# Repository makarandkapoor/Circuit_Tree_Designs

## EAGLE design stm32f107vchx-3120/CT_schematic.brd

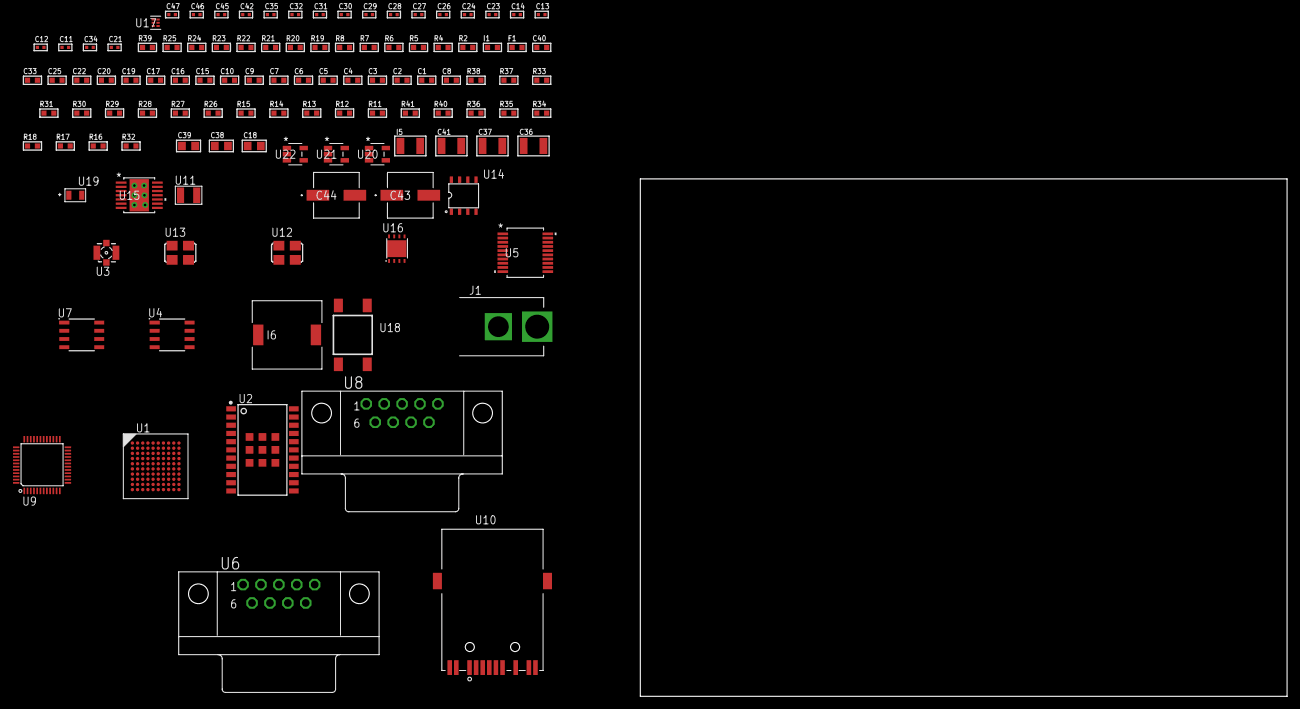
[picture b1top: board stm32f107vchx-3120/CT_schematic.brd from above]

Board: 2 copper layers, 100.0 x 80.0 mm, 111 parts (0 on the bottom side), 78 nets, no tracks yet.

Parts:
C1, C10, C15, C16, C17, C19, C20, C22, C25, C33, C40: 1e-06; C0603
C2, C3, C4, C5, C6, C7: 1e-07; C0603
C8: 4.7e-06; C0603
C9: 1e-08; C0603
C11, C12: 1e-11; C0402
C13, C23, C26, C28, C29, C35, C42: 1e-07; C0402
C14, C24, C27, C30, C31, C32, C45, C46, C47: 1e-08; C0402
C18: 4.7e-06; C0805
C21: 2.2e-08; C0402
C34: 3.3e-09; C0402
C36, C37: 2.2e-05; C1210
C38, C39: 1e-05; C0805
C41: 1e-05; C1210
C43, C44: 0.0001; EXV-9H
F1: 240.0; L0603
I1: 97.0; R0603
I5: 1.5e-05; L1210
I6: 5.2e-06; DR1040
J1: PJ-037B; PJ-037B_PACKAGE
R2: 1000.0; R0603
R4, R5, R6, R25: 4700.0; R0603
R7, R8: 2200.0; R0603
R11, R12, R13, R14, R15, R26, R27, R28, R29, R30, R31, R37, R38: 10000.0; R0603
R16, R17, R18, R34, R36: 100000.0; R0603
R19: 120.0; R0603
R20, R21: 0.1; R0603
R22, R23: 200.0; R0603
R24: 2490.0; R0603
R32: 71007.101651032; R0603
R33: 22000.0; R0603
R35: 300000.0; R0603
R39: 9100.0; R0603
R40: 680000.0; R0603
R41: 120000.0; R0603
U1: stm32f107vch6; LFBGA100
U2: A2200-A
U3: 73412-0114; COAXIAL_C
U4: AT25040B-SSHL-T; SOIC-8
U5: MAX3218EAP+T; SSOP-20
U6, U8: 182-009-113R531; 182-009-MALE
U7: MCP2562-E/SN; SOIC-8
U9: RTL8201FL-VB-CG
U10: 7498011122R
U11: ABS07-32.768KHZ-7-T
U12: ASFL1-25MHZ-NCS; ASFL1
U13: ASFL1-50MHZ-NCS; ASFL1
U14: idt74fct38072; IDT74FCT38072
U15: tps54225PWP; HTSSOP14
U16: LP2951ACSDX/NOPB; WSON-8
U17: TPS3895ADRYR; SON-6
U18: 4-1437565-2; SW_4-1437565-2
U19: Q65110A2395; LGM67K-G1J2-24-Z
U20, U21, U22: nc7sz125m5x; NC7SZ125M5X

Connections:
CLK_CRYSTAL_U1_A1: C11.1, U1.A1, U11.1
CLK_CRYSTAL_U1_B1: C12.1, U1.B1, U11.2
CLK_U1_C1: U1.C1, U12.3
CLK_U1_H2: U1.H2, U14.7
CLK_U9_43: U9.43, U14.6
CLK_U14_3: U13.3, U14.3
GND: C1.2, C2.2, C3.2, C4.2, C5.2, C6.2, C7.2, C8.2, C9.2, C10.2, C11.2, C12.2, C13.2, C14.2, C15.2, C16.2, C17.2, C19.2, C20.2, C21.2, C22.2, C23.2, C24.2, C25.2, C26.2, C27.2, C28.2, C29.2, C30.2, C31.2, C32.2, C33.2, C34.2, C36.2, C37.2, C38.2, C39.2, C40.2, C41.2, C42.2, C43.2, C44.2, C45.2, C46.2, C47.2, J1.2, R2.2, R11.2, R20.2, R21.2, R24.2, R29.2, R33.2, R36.2, R39.2, R41.2, U1.C2, U1.E4, U1.E5, U1.E6, U1.E7, U1.G1, U1.H1, U2.7, U2.8, U2.23, U2.24, U2.25, U2.26, U2.27, U2.28, U2.29, U2.30, U2.31, U4.4, U5.5, U5.17, U5.20, U6.5, U7.2, U7.8, U8.5, U9.7, U9.20, U9.33, U9.42, U9.47, U12.2, U13.2, U14.4, U14.5, U14.8, U15.5, U15.8, U15.9, U15.15, U16.3, U16.4, U16.PAD, U17.2, U19.C, U20.1, U20.3, U21.1, U21.3, U22.1, U22.3
NET_U1_A5: R8.1, U1.A5, U2.16
NET_U1_B4: R7.1, U1.B4, U2.15
NET_U1_D5: R11.1, U1.D5
NET_U1_E1: R6.1, U1.E1, U22.4
NET_U1_K1: C9.1, C10.1, F1.1, U1.J1, U1.K1
NET_U1_K10: U18.3, U18.4
NET_U2_2: R12.2, U2.2
NET_U2_17: R12.1, U2.17
NET_U2_22: R5.1, U2.22, U21.4
NET_U3_1: U2.11, U3.1
NET_U3_2: U2.10, U3.2, U3.3, U3.4
NET_U4_3: R13.1, U4.3
NET_U4_7: R15.1, U4.7
NET_U5_1: I5.1, U5.1
NET_U5_2: R16.1, U5.2
NET_U5_3: R17.1, U5.3
NET_U5_4: R18.1, U5.4
NET_U5_15: C17.1, U5.15
NET_U5_16: C18.2, U5.16
NET_U5_18: C18.1, U5.18
NET_U5_19: C16.1, U5.19
NET_U6_2: U5.12, U6.2
NET_U6_3: U5.14, U6.3
NET_U6_7: U5.11, U6.7
NET_U6_8: U5.13, U6.8
NET_U7_6: R19.2, U7.6
NET_U8_2: R19.2, U7.6, U8.2
NET_U8_3: R19.1, U7.7, U8.3
NET_U9_6: C22.1, C23.1, C24.1, I1.1, U9.6, U9.41
NET_U9_10: R29.1, U9.10
NET_U9_13: R26.1, U9.13
NET_U9_18: R30.1, U9.18
NET_U9_29: R4.1, U9.29, U20.4
NET_U9_32: R25.1, U9.32
NET_U9_34: R27.1, U9.34
NET_U9_35: R28.1, U9.35
NET_U9_39: R31.1, U9.39
NET_U9_40: C29.1, U9.40
NET_U9_46: R24.1, U9.46
NET_U9_48: C28.1, U9.48
NET_U10_1: U9.1, U10.1
NET_U10_3: U9.2, U10.3
NET_U10_4: U9.4, U10.4
NET_U10_5: C21.1, U10.2, U10.5
NET_U10_6: U9.5, U10.6
NET_U10_8: R21.1, U10.8
NET_U10_10: R22.1, U10.10
NET_U10_12: R23.1, U10.12
NET_U10_13: R20.1, U10.13, U10.14
NET_U15_2: R32.2, R33.1, U15.2
NET_U15_3: C33.1, U15.3
NET_U15_4: C34.1, U15.4
NET_U15_10: C35.1, I6.1, U15.10, U15.11
NET_U15_12: C35.2, U15.12
NET_U16_5: R34.1, U16.5
NET_U16_7: R35.2, R36.1, U16.7
NET_U17_1: R38.1, R39.1, U17.1
NET_U17_3: R40.2, R41.1, U17.3
NET_U17_4: R37.1, U17.4, U20.2, U21.2, U22.2
NET_U18_1: R2.1, U18.1, U18.2
PROC_CAN1_RX: U1.C10, U7.4
PROC_CAN1_TX: U1.A4, U7.1
PROC_SPI1_MISO: U1.A6, U4.2
PROC_SPI1_MOSI: U1.C5, U4.5
PROC_SPI1_NSS: R14.1, U1.A8, U4.1
PROC_SPI1_SCK: U1.A7, U4.6
PROC_UART4_RX: U1.B8, U5.9
PROC_UART4_TX: U1.B9, U5.7
VCC_S1_6V4: C38.1, C39.1, C40.1, C43.1, C44.1, J1.1, U15.7, U15.13, U15.14, U16.8
VCC_TIER1_3V3: C1.1, C2.1, C3.1, C4.1, C5.1, C6.1, C7.1, C8.1, C13.1, C14.1, C15.1, C20.1, C25.1, C26.1, C27.1, C30.1, C31.1, C32.1, C36.1, C37.1, C42.1, C45.1, C46.1, C47.1, F1.2, I1.2, I5.2, I6.2, R4.2, R5.2, R6.2, R7.2, R8.2, R13.2, R14.2, R15.2, R16.2, R17.2, R18.2, R25.2, R26.2, R27.2, R28.2, R30.2, R31.2, R32.1, R37.2, R38.2, R40.1, U1.B2, U1.D2, U1.F4, U1.F5, U1.F6, U1.F7, U2.20, U4.8, U5.6, U7.5, U9.15, U9.21, U9.37, U10.9, U10.11, U12.4, U13.4, U14.1, U14.2, U15.1, U17.6, U20.5, U21.5, U22.5
VCC_TIER1_5V0: C19.1, C41.1, R34.2, R35.1, U7.3, U16.1

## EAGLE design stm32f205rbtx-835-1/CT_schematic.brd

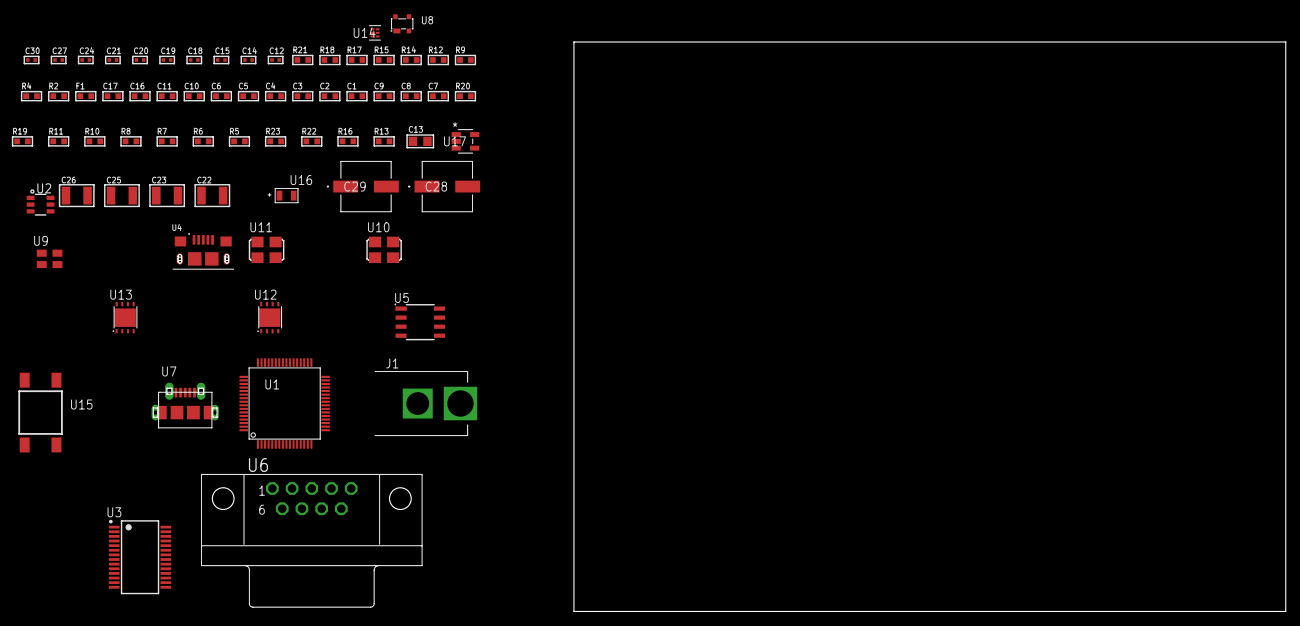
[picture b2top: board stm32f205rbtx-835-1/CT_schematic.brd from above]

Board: 2 copper layers, 70 parts (0 on the bottom side), 43 nets, no tracks yet.

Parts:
C1, C11, C16, C17: 1e-06; C0603
C2, C3, C4, C5, C6: 1e-07; C0603
C7: 4.7e-06; C0603
C8, C9: 2.2e-06; C0603
C10: 1e-08; C0603
C12, C14, C15, C27: 1e-07; C0402
C13: 4.7e-06; C0805
C18, C19, C20, C21, C24, C30: 1e-08; C0402
C22, C23, C25, C26: 1e-05; C1210
C28, C29: 0.0001; EXV-9H
F1: 240.0; L0603
J1: PJ-037B; PJ-037B_PACKAGE
R2, R15, R18: 1000.0; R0603
R4, R9: 4700.0; R0603
R5: 47000.0; R0603
R6, R7, R8, R10, R11, R19, R20: 10000.0; R0603
R12: 120.0; R0603
R13, R16: 100000.0; R0603
R14: 2231.0; R0603
R17: 3900.0; R0603
R21: 9100.0; R0603
R22: 680000.0; R0603
R23: 120000.0; R0603
U1: STM32F205RBT7; LQFP64
U2: MAX4995AAUT+T; SOT-23-6
U3: FT232RL-REEL; SSOP-28
U4: 10118193-0001LF; FCI_10118193-0001LF
U5: MCP2562-E/SN; SOIC-8
U6: 182-009-113R531; 182-009-MALE
U7: 47590-0001; MICRO_USB_AB
U8: prtr5v0u2ax; SOT143B
U9: ASEK-32.768KHz-ECST; ASEK
U10: ASFL1-12MHZ-NCS; ASFL1
U11: ASFL1-25MHZ-NCS; ASFL1
U12, U13: LP3878SDX-ADJ/NOPB; WSON-8
U14: TPS3895ADRYR; SON-6
U15: 4-1437565-2; SW_4-1437565-2
U16: Q65110A2395; LGM67K-G1J2-24-Z
U17: nc7sz125m5x; NC7SZ125M5X

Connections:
CLK_U1_3: U1.3, U9.3
CLK_U1_5: U1.5, U11.3
CLK_U3_27: U3.27, U10.3
GND: C1.2, C2.2, C3.2, C4.2, C5.2, C6.2, C7.2, C8.2, C9.2, C10.2, C11.2, C12.2, C13.2, C14.2, C15.2, C16.2, C17.2, C18.2, C19.2, C20.2, C21.2, C22.2, C23.2, C24.2, C25.2, C26.2, C27.2, C28.2, C29.2, C30.2, J1.2, R2.2, R5.2, R6.2, R8.2, R11.2, R15.2, R18.2, R21.2, R23.2, U1.12, U1.18, U1.63, U2.2, U3.7, U3.18, U3.21, U3.25, U3.26, U4.5, U4.6, U4.7, U4.8, U4.9, U5.2, U5.8, U6.5, U7.5, U7.6, U7.7, U7.8, U7.9, U8.1, U9.2, U10.2, U11.2, U12.3, U12.PAD, U13.3, U13.PAD, U14.2, U16.C, U17.1, U17.3
NET_U1_7: R4.1, U1.7, U17.4
NET_U1_13: C10.1, C11.1, F1.1, U1.13
NET_U1_31: C8.1, U1.31
NET_U1_47: C9.1, U1.47
NET_U1_59: U15.3, U15.4
NET_U1_60: R6.1, U1.60
NET_U2_3: R5.1, U2.3
NET_U3_14: R10.1, U3.14
NET_U3_17: C14.1, U3.17
NET_U3_19: R11.1, U3.19
NET_U4_1: R9.1, U4.1
NET_U4_2: U3.16, U4.2
NET_U4_3: U3.15, U4.3
NET_U5_6: R12.2, U5.6
NET_U6_2: R12.2, U5.6, U6.2
NET_U6_3: R12.1, U5.7, U6.3
NET_U12_1: C21.1, U12.1
NET_U12_6: R14.2, R15.1, U12.6
NET_U12_8: R13.1, U12.8
NET_U13_1: C24.1, U13.1
NET_U13_6: R17.2, R18.1, U13.6
NET_U13_8: R16.1, U13.8
NET_U14_1: R20.1, R21.1, U14.1
NET_U14_3: R22.2, R23.1, U14.3
NET_U14_4: R19.1, U14.4, U17.2
NET_U15_1: R2.1, U15.1, U15.2
PROC_CAN1_RX: U1.61, U5.4
PROC_CAN1_TX: U1.62, U5.1
PROC_GPIO_TO_U1_USB_FAULT: R7.1, U1.4, U2.6
PROC_GPIO_TO_U1_VBUS_EN: R8.1, U1.2, U2.4
PROC_UART4_RX: U1.15, U3.1
PROC_UART4_TX: U1.14, U3.5
PROC_USB_OTG_FS_DM: U1.44, U7.2, U8.3
PROC_USB_OTG_FS_DP: U1.45, U7.3, U8.2
PROC_USB_OTG_FS_ID: U1.43, U7.4
PROC_USB_OTG_FS_VBUS: U1.42, U2.1, U7.1, U8.4
VCC_S1_13V4: C22.1, C25.1, C28.1, C29.1, J1.1, R13.2, R16.2, U12.4, U13.4
VCC_TIER1_3V3: C1.1, C2.1, C3.1, C4.1, C5.1, C6.1, C7.1, C12.1, C13.1, C15.1, C17.1, C18.1, C19.1, C20.1, C23.1, C27.1, C30.1, F1.2, R4.2, R7.2, R10.2, R14.1, R19.2, R20.2, R22.1, U1.1, U1.19, U1.32, U1.48, U1.64, U3.4, U3.20, U5.5, U9.4, U10.4, U11.4, U12.5, U14.6, U17.5
VCC_TIER1_5V0: C16.1, C26.1, R17.1, U2.5, U5.3, U13.5

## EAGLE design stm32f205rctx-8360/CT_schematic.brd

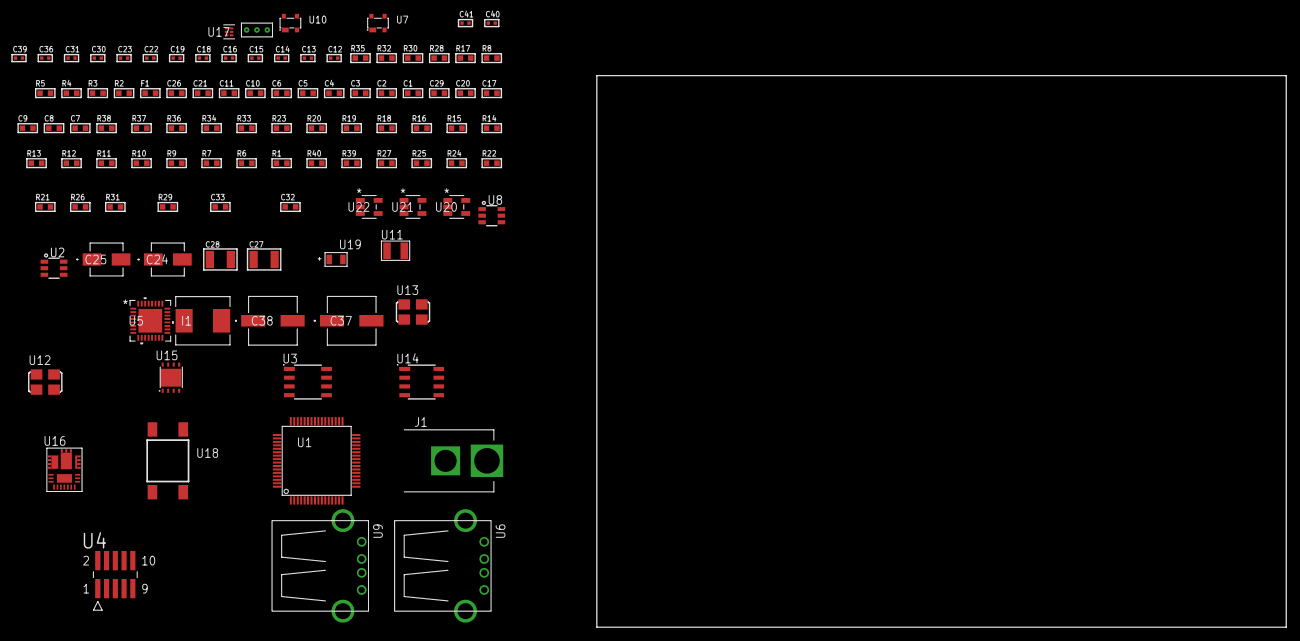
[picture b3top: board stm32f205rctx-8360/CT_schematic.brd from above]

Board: 2 copper layers, 100.0 x 80.0 mm, 105 parts (0 on the bottom side), 76 nets, no tracks yet.

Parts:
C1, C11: 1e-06; C0603
C2, C3, C4, C5, C6: 1e-07; C0603
C7: 4.7e-06; C0603
C8, C9, C17, C20, C29: 2.2e-06; C0603
C10: 1e-08; C0603
C12, C13: 1e-11; C0402
C14, C22, C23, C39, C40, C41: 1e-08; C0402
C15, C16, C18, C19, C30, C31, C36: 1e-07; C0402
C21: 0.0001; R0603
C24: 1e-06; EXV-9B
C25: 2.2e-06; EXV-9B
C26: 8e-07; R0603
C27: 1e-05; C1210
C28: 0.0001; C1210
C32: 8.8006443804346e-09; R0603
C33: 3.0002196751482e-07; R0603
C37, C38: 0.0001; EXV-9H
F1: 240.0; L0603
I1: 6.8e-07; IND25X25CZ
J1: PJ-037B; PJ-037B_PACKAGE
R1, R7, R9, R10, R11, R12, R13, R14, R15, R16, R19, R20, R36, R37: 10000.0; R0603
R2: 1000.0; R0603
R3: 910.0; R0603
R4, R5: 4700.0; R0603
R6, R18, R23: 47000.0; R0603
R8: 1270.0; R0603
R17: 5.0; R0603
R21, R22, R24, R25, R27: 100000.0; R0603
R26: 153694.38; R0603
R28: 0.1; R0603
R29: 4030.2416170974; R0603
R30: 453.0; R0603
R31: 57.923764705882; R0603
R32: 130.0; R0603
R33: 39000.0; R0603
R34: 49900.0; R0603
R35: 5100.0; R0603
R38: 82000.0; R0603
R39: 300000.0; R0603
R40: 120000.0; R0603
U1: STM32F205RCT7; LQFP64
U2, U8: MAX4995AAUT+T; SOT-23-6
U3: AT25010B-SSHL-T; SOIC-8
U4: FTSH-105-01-L-DV-K; SAMTEC_FTSH-105-01-L-DV-K
U5: TUSB1210BRHBR; RHB32_3P45X3P45
U6, U9: 61400416021; USB-A-H
U7, U10: prtr5v0u2ax; SOT143B
U11: ABS07-32.768KHZ-7-T
U12: ASFL1-19.2MHZ-NCS; ASFL1
U13: ASFL1-25MHZ-NCS; ASFL1
U14: LP2954AIMX/NOPB; LP2954
U15: LP2951ACSDX/NOPB; WSON-8
U16: IR3899MTR1PBF
U17: TPS3895ADRYR; SON-6
U18: 4-1437565-2; SW_4-1437565-2
U19: Q65110A2395; LGM67K-G1J2-24-Z
U20, U21, U22: nc7sz125m5x; NC7SZ125M5X
U23: Dummy; DUMMY_PACKAGE_226

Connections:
CLK_CRYSTAL_U1_3: C12.1, U1.3, U11.1
CLK_CRYSTAL_U1_4: C13.1, U1.4, U11.2
CLK_U1_5: U1.5, U13.3
CLK_U5_1: U5.1, U12.3
GND: C1.2, C2.2, C3.2, C4.2, C5.2, C6.2, C7.2, C8.2, C9.2, C10.2, C11.2, C12.2, C13.2, C14.2, C15.2, C16.2, C17.2, C18.2, C19.2, C20.2, C21.2, C22.2, C23.2, C24.2, C25.2, C26.2, C27.2, C29.2, C30.2, C31.2, C36.2, C37.2, C38.2, C39.2, C40.2, C41.2, J1.2, R2.2, R6.2, R7.2, R8.2, R10.2, R17.2, R18.2, R20.2, R24.2, R27.2, R28.1, R28.2, R30.2, R33.2, R35.2, R38.2, R40.2, U1.12, U1.18, U1.63, U2.2, U3.4, U4.3, U4.5, U5.23, U5.33, U6.4, U6.5, U6.6, U7.1, U8.2, U9.4, U9.5, U9.6, U10.1, U12.2, U13.2, U14.4, U15.3, U15.4, U15.PAD, U16.4, U16.11, U16.17, U17.2, U19.C, U20.2, U20.3, U21.1, U21.3, U22.1, U22.3, U23.1
NET_U1_7: R4.1, U1.7, U21.4
NET_U1_13: C10.1, C11.1, F1.1, U1.13
NET_U1_31: C8.1, U1.31
NET_U1_47: C9.1, U1.47
NET_U1_60: R7.1, U1.60
NET_U1_61: R3.1, U1.61, U19.A
NET_U1_62: R1.1, U1.62, U18.3, U18.4
NET_U2_3: R6.1, U2.3
NET_U3_3: R11.1, U3.3
NET_U3_7: R13.1, U3.7
NET_U4_9: R17.1, U4.9
NET_U5_11: R19.1, U5.11
NET_U5_12: C20.1, U5.12
NET_U5_14: R20.1, U5.14
NET_U5_20: C17.1, U5.20
NET_U5_27: R5.1, U5.27, U22.4
NET_U6_1: C21.1, U5.22, U6.1, U7.4, U8.1
NET_U6_2: U5.19, U6.2, U7.3
NET_U6_3: U5.18, U6.3, U7.2
NET_U8_3: R18.1, U8.3
NET_U8_4: U5.17, U8.4
NET_U14_3: R22.1, U14.3
NET_U14_5: R21.1, U14.5
NET_U14_7: R23.2, R24.1, U14.7
NET_U15_5: R25.1, U15.5
NET_U15_7: R26.2, R27.1, U15.7
NET_U16_1: C32.1, R29.1, R30.1, R31.1, R32.1, U16.1, U16.8
NET_U16_2: C31.1, U16.2
NET_U16_3: C32.2, C33.1, C33.2, U16.3
NET_U16_5: R33.1, U16.5
NET_U16_10: C29.1, U16.10
NET_U16_12: C28.1, I1.1, U16.12
NET_U16_14: C28.2, U16.14
NET_U16_15: R34.1, R35.1, U16.15
NET_U16_ATNET_3: I1.2, R29.2
NET_U16_ATNET_4: C33.2, R31.2
NET_U17_1: R37.1, R38.1, U17.1
NET_U17_3: R39.2, R40.1, U17.3
NET_U17_4: R36.1, U17.4, U20.4, U21.2, U22.2
NET_U18_1: R2.1, U18.1, U18.2
PROC_GPIO_TO_U1_USB_FAULT: R9.1, U1.6, U2.6
PROC_GPIO_TO_U1_VBUS_EN: R10.1, U1.2, U2.4
PROC_SPI3_MISO: U1.52, U3.2
PROC_SPI3_MOSI: U1.53, U3.5
PROC_SPI3_NSS: R12.1, U1.20, U3.1
PROC_SPI3_SCK: U1.51, U3.6
PROC_SYS_JTCK_SWCLK: R15.1, U1.49, U4.4
PROC_SYS_JTDO_SWO: U1.55, U4.6
PROC_SYS_JTMS_SWDIO: R16.1, U1.46, U4.2
PROC_TIM1_CH1: U1.41, U23.3
PROC_TIM1_CH3: R8.1, U1.43, U23.2
PROC_USB_OTG_FS_DM: U1.44, U9.2, U10.3
PROC_USB_OTG_FS_DP: U1.45, U9.3, U10.2
PROC_USB_OTG_FS_VBUS: U1.42, U2.1, U9.1, U10.4
PROC_USB_OTG_HS_ULPI_CK: U1.21, U5.26
PROC_USB_OTG_HS_ULPI_D0: U1.17, U5.3
PROC_USB_OTG_HS_ULPI_D1: U1.26, U5.4
PROC_USB_OTG_HS_ULPI_D2: U1.27, U5.5
PROC_USB_OTG_HS_ULPI_D3: U1.29, U5.6
PROC_USB_OTG_HS_ULPI_D4: U1.30, U5.7
PROC_USB_OTG_HS_ULPI_D5: U1.33, U5.9
PROC_USB_OTG_HS_ULPI_D6: U1.34, U5.10
PROC_USB_OTG_HS_ULPI_D7: U1.57, U5.13
PROC_USB_OTG_HS_ULPI_DIR: U1.10, U5.31
PROC_USB_OTG_HS_ULPI_NXT: U1.11, U5.2
PROC_USB_OTG_HS_ULPI_STP: U1.8, U5.29
RST_OUT_U4_JTAG_RST_B: R14.1, U4.10, U20.1
VCC_S1_17V0: C24.1, C26.1, C30.1, C37.1, C38.1, J1.1, R22.2, R34.2, U14.8, U15.8, U16.9
VCC_TIER1_1V8: C1.1, C2.1, C3.1, C4.1, C5.1, C6.1, C7.1, C14.1, C15.1, C18.1, C19.1, C25.1, C36.1, C39.1, C40.1, C41.1, F1.2, R1.2, R3.2, R4.2, R5.2, R9.2, R11.2, R12.2, R13.2, R14.2, R15.2, R16.2, R19.2, R21.2, R23.1, R36.2, R37.2, R39.1, U1.1, U1.19, U1.32, U1.48, U1.64, U3.8, U4.1, U5.28, U5.30, U5.32, U14.1, U17.6, U20.5, U21.5, U22.5
VCC_TIER1_3V3: C16.1, C22.1, C23.1, C27.1, R25.2, R26.1, U5.21, U12.4, U13.4, U15.1
VCC_TIER1_5V0: I1.2, R29.2, U2.5, U8.5

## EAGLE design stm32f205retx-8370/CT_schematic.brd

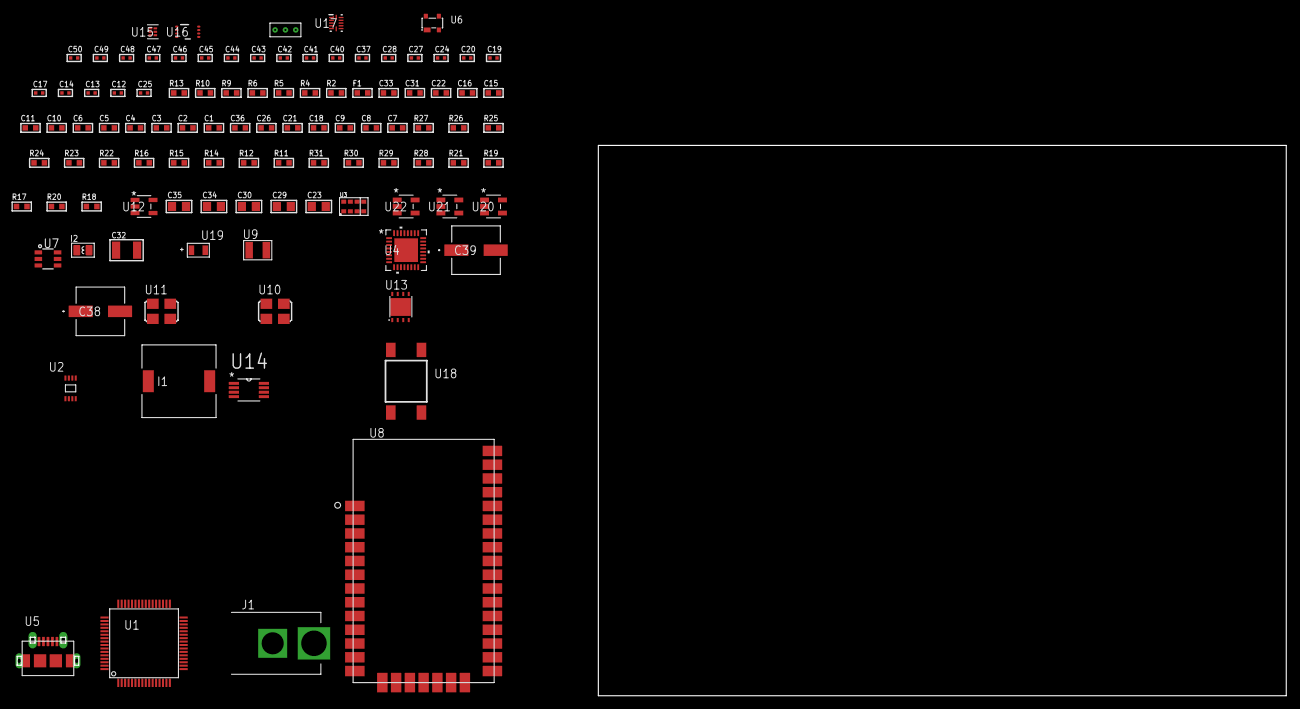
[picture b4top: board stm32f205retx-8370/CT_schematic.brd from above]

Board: 2 copper layers, 104 parts (0 on the bottom side), 65 nets, no tracks yet.

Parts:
C1, C11, C15, C16, C22, C31, C33: 1e-06; C0603
C2, C3, C4, C5, C6: 1e-07; C0603
C7: 4.7e-06; C0603
C8, C9, C18, C21: 2.2e-06; C0603
C10: 1e-08; C0603
C12, C13: 1e-11; C0402
C14, C27, C28, C40, C42, C44, C46, C48, C49, C50: 1e-08; C0402
C17, C19, C20, C24, C37, C41, C43, C45, C47: 1e-07; C0402
C23, C29, C30, C34, C35: 1e-05; C0805
C25: 4.7e-11; C0402
C26: 8.2e-12; C0603
C32: 1e-05; C1210
C36: 1.6e-09; C0603
C38, C39: 0.0001; EXV-9H
F1: 240.0; L0603
I1: 7e-06; DR1040
I2: 3.3e-06; L0806
J1: PJ-037B; PJ-037B_PACKAGE
R2: 1000.0; R0603
R4, R5, R6: 4700.0; R0603
R9, R10: 2200.0; R0603
R11, R12, R15, R16, R25, R26: 10000.0; R0603
R13: 22.0; R0603
R14, R22: 47000.0; R0603
R17: 490000.0; R0603
R18: 1000000.0; R0603
R19, R21: 100000.0; R0603
R20: 153694.38; R0603
R23: 56000.0; R0603
R24: 18000.0; R0603
R27: 82000.0; R0603
R28: 300000.0; R0603
R29: 120000.0; R0603
R30, R31: 200000.0; R0603
U1: STM32F205RET7; LQFP64
U2: 24AA02T-I/MNY; TDFN-8/6MM
U3: TMD27711; SMD-8
U4: TUSB1210BRHBR; RHB32_3P45X3P45
U5: 47590-0001; MICRO_USB_AB
U6: prtr5v0u2ax; SOT143B
U7: MAX4995AAUT+T; SOT-23-6
U8: XB24CZ7UIS-004
U9: ABS07-32.768KHZ-7-T
U10: ASFL1-19.2MHZ-NCS; ASFL1
U11: ASFL1-25MHZ-NCS; ASFL1
U12: ltc3406es5; TSOT-23-5
U13: LP2951ACSDX/NOPB; WSON-8
U14: TPS61085DGKR; MSOP-8
U15: TPS3895ADRYR; SON-6
U16: LSF0102DCTR; DCU0008A_N
U17: LSF0204DRUTR; RUT0012A
U18: 4-1437565-2; SW_4-1437565-2
U19: Q65110A2395; LGM67K-G1J2-24-Z
U20, U21, U22: nc7sz125m5x; NC7SZ125M5X
U23: Dummy; DUMMY_PACKAGE_217

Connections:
CLK_CRYSTAL_U1_3: C12.1, U1.3, U9.1
CLK_CRYSTAL_U1_4: C13.1, U1.4, U9.2
CLK_U1_5: U1.5, U11.3
CLK_U4_1: U4.1, U10.3
GND: C1.2, C2.2, C3.2, C4.2, C5.2, C6.2, C7.2, C8.2, C9.2, C10.2, C11.2, C12.2, C13.2, C14.2, C15.2, C16.2, C17.2, C18.2, C19.2, C20.2, C21.2, C22.2, C23.2, C24.2, C25.2, C26.2, C27.2, C28.2, C29.2, C30.1, C30.2, C31.2, C32.2, C33.2, C34.2, C35.1, C35.2, C36.1, C36.2, C37.2, C38.2, C39.2, C40.2, C41.2, C42.2, C43.2, C44.2, C45.2, C46.2, C47.2, C48.2, C49.2, C50.2, J1.2, R2.2, R11.2, R14.2, R16.2, R17.2, R21.2, R24.2, R27.2, R29.2, U1.12, U1.18, U1.63, U2.4, U3.3, U4.33, U5.5, U5.6, U5.7, U5.8, U5.9, U6.1, U7.2, U8.1, U8.11, U8.13, U8.22, U8.35, U10.2, U11.2, U12.2, U13.3, U13.4, U13.PAD, U14.4, U15.2, U16.1, U17.6, U19.C, U20.1, U20.3, U21.1, U21.3, U22.1, U22.3, U23.1
NET_U1_7: R5.1, U1.7, U21.4
NET_U1_13: C10.1, C11.1, F1.1, U1.13
NET_U1_31: C8.1, U1.31
NET_U1_40: R10.1, U1.40, U2.5
NET_U1_41: R9.1, U1.41, U2.6
NET_U1_47: C9.1, U1.47
NET_U1_60: R11.1, U1.60
NET_U1_62: U18.3, U18.4
NET_U3_4: C16.1, R13.1, U3.4
NET_U3_7: R12.1, U3.7
NET_U4_11: R15.1, U4.11
NET_U4_12: C21.1, U4.12
NET_U4_14: R16.1, U4.14
NET_U4_20: C18.1, U4.20
NET_U4_27: R6.1, U4.27, U22.4
NET_U5_1: C22.1, U4.22, U5.1, U6.4, U7.1
NET_U5_2: U4.19, U5.2, U6.3
NET_U5_3: U4.18, U5.3, U6.2
NET_U5_4: U4.23, U5.4
NET_U7_3: R14.1, U7.3
NET_U7_4: U4.17, U7.4
NET_U8_6: R4.1, U8.6, U20.4
NET_U12_3: I1.1, U12.3
NET_U12_5: R17.1, R18.1, U12.5
NET_U12_ATNET_3: I1.2, R18.2
NET_U13_5: R19.1, U13.5
NET_U13_7: R20.2, R21.1, U13.7
NET_U14_1: R22.1, U14.1
NET_U14_2: R23.1, R24.1, U14.2
NET_U14_5: I2.1, U14.5
NET_U15_1: R26.1, R27.1, U15.1
NET_U15_3: R28.2, R29.1, U15.3
NET_U15_4: R25.1, U15.4, U20.2, U21.2, U22.2
NET_U16_8: R30.1, U16.8
NET_U17_12: R31.1, U17.12
NET_U18_1: R2.1, U18.1, U18.2
PROC_I2C1_SCL_TOXCVR: U3.2, U16.5
PROC_I2C1_SDA_TOXCVR: U3.8, U16.6
PROC_SPI1_MISO_TOXCVR: U8.17, U17.9
PROC_SPI1_MOSI_TOXCVR: U8.16, U17.10
PROC_SPI1_NSS_TOXCVR: U8.15, U17.7
PROC_SPI1_SCK_TOXCVR: U8.14, U17.8
PROC_TIM1_CH2: U1.42, U23.2
PROC_TIM1_CH4: U1.44, U23.3
PROC_USB_OTG_HS_ULPI_CK: U1.21, U4.26
PROC_USB_OTG_HS_ULPI_D0: U1.17, U4.3
PROC_USB_OTG_HS_ULPI_D1: U1.26, U4.4
PROC_USB_OTG_HS_ULPI_D2: U1.27, U4.5
PROC_USB_OTG_HS_ULPI_D3: U1.29, U4.6
PROC_USB_OTG_HS_ULPI_D4: U1.30, U4.7
PROC_USB_OTG_HS_ULPI_D5: U1.33, U4.9
PROC_USB_OTG_HS_ULPI_D6: U1.34, U4.10
PROC_USB_OTG_HS_ULPI_D7: U1.57, U4.13
PROC_USB_OTG_HS_ULPI_DIR: U1.10, U4.31
PROC_USB_OTG_HS_ULPI_NXT: U1.11, U4.2
PROC_USB_OTG_HS_ULPI_STP: U1.8, U4.29
VCC_S1_5V2: C29.1, C31.1, C33.1, C34.1, C38.1, C39.1, I2.2, J1.1, U12.4, U13.8, U14.3, U14.6
VCC_TIER1_1V8: C1.1, C2.1, C3.1, C4.1, C5.1, C6.1, C7.1, C14.1, C19.1, C20.1, C30.2, C37.1, C42.1, C43.1, C46.1, C47.1, C48.1, C49.1, C50.1, F1.2, I1.2, R5.2, R6.2, R9.2, R10.2, R15.2, R18.2, R25.2, R26.2, R28.1, R31.2, U1.1, U1.19, U1.32, U1.48, U1.64, U2.7, U2.8, U4.28, U4.30, U4.32, U15.6, U16.2, U17.1, U20.5, U21.5, U22.5
VCC_TIER1_3V3: C15.1, C17.1, C23.1, C24.1, C25.1, C26.1, C27.1, C28.1, C32.1, C40.1, C41.1, C44.1, C45.1, R4.2, R12.2, R13.2, R19.2, R20.1, R30.2, U3.1, U4.21, U8.2, U8.27, U10.4, U11.4, U13.1, U16.7, U17.11
VCC_TIER1_5V0: C35.2, R23.2, U7.5

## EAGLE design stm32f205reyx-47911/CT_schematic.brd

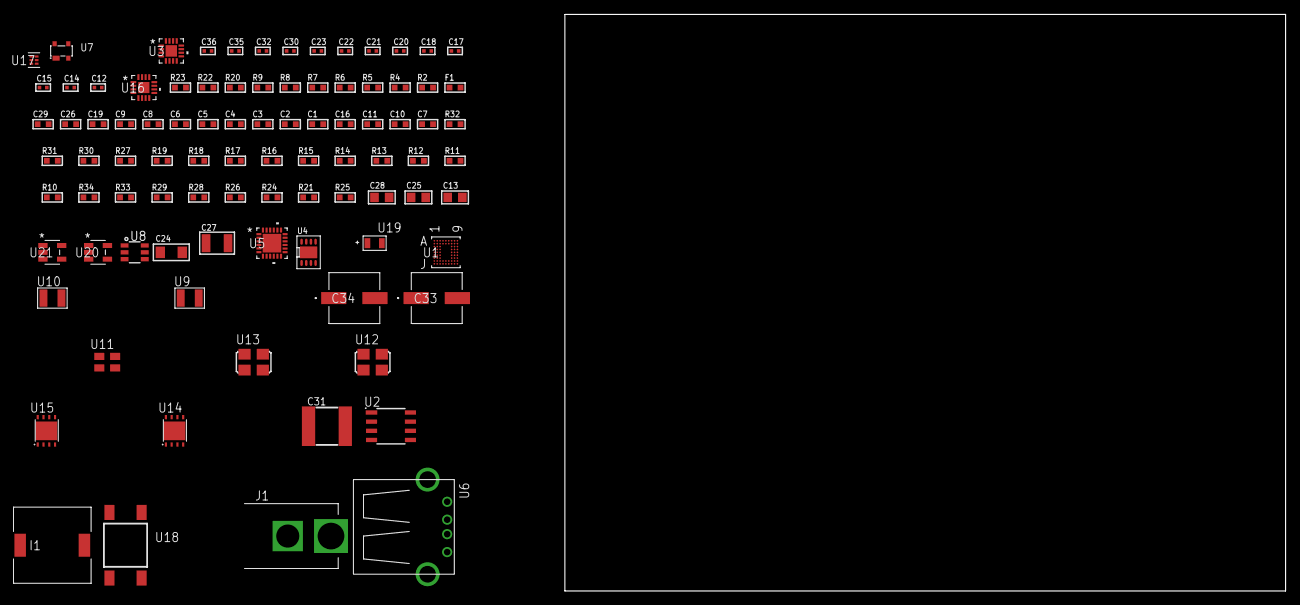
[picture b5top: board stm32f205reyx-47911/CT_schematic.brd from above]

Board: 2 copper layers, 100.0 x 80.0 mm, 92 parts (0 on the bottom side), 68 nets, no tracks yet.

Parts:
C1, C9, C26, C29: 1e-06; C0603
C2, C3, C4, C5, C6: 1e-07; C0603
C7: 4.7e-06; C0603
C8: 1e-08; C0603
C10, C11, C16: 2.2e-06; C0603
C12, C15, C17, C18, C20, C21, C22, C23, C35, C36: 1e-08; C0402
C13: 4.7e-06; C0805
C14, C30, C32: 1e-07; C0402
C19: 0.0001; R0603
C24: 1e-05; C1206
C25, C28: 1e-05; C0805
C27: 1e-05; C1210
C31: 6.8e-05; 2220
C33, C34: 0.0001; EXV-9H
F1: 240.0; L0603
I1: 5.2e-06; DR1040
J1: PJ-037B; PJ-037B_PACKAGE
R2, R23: 1000.0; R0603
R4, R5: 4700.0; R0603
R6, R7, R8, R9: 2200.0; R0603
R10, R11, R12, R13, R14, R15, R16, R17, R18, R30, R31: 10000.0; R0603
R19: 47000.0; R0603
R20: 8060.0; R0603
R21, R24, R26: 100000.0; R0603
R22: 806.0; R0603
R25: 153694.38; R0603
R27: 20000.0; R0603
R28: 150000.0; R0603
R29, R33: 300000.0; R0603
R32: 82000.0; R0603
R34: 120000.0; R0603
U1: STM32F205REY6; WLCSP66
U2: AT25320B-SSHL-T; SOIC-8
U3: M41T65Q6F; M41T65_QFN-16
U4: PCF85063TP/1Z; SON-8
U5: USB3317C-CP-TR; QFN-24
U6: 61400416021; USB-A-H
U7: prtr5v0u2ax; SOT143B
U8: MAX4995AAUT+T; SOT-23-6
U9, U10: ABS07-32.768KHZ-7-T
U11: ASEK-32.768KHz-ECST; ASEK
U12: ASFL1-25MHZ-NCS; ASFL1
U13: ASFL1-26MHZ-NCS; ASFL1
U14: LP3878SDX-ADJ/NOPB; WSON-8
U15: LP2951ACSDX/NOPB; WSON-8
U16: LTC3601EUD#PBF; QFN-16_EP
U17: TPS3895ADRYR; SON-6
U18: 4-1437565-2; SW_4-1437565-2
U19: Q65110A2395; LGM67K-G1J2-24-Z
U20, U21: nc7sz125m5x; NC7SZ125M5X

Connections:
CLK_CRYSTAL_U3_1: U3.1, U9.1
CLK_CRYSTAL_U3_2: U3.2, U9.2
CLK_CRYSTAL_U4_1: U4.1, U10.1
CLK_CRYSTAL_U4_2: U4.2, U10.2
CLK_U1_B9: U1.B9, U11.3
CLK_U1_E9: U1.E9, U12.3
CLK_U5_23: U5.23, U13.3
GND: C1.2, C2.2, C3.2, C4.2, C5.2, C6.2, C7.2, C8.2, C9.2, C10.2, C11.2, C12.2, C13.2, C14.2, C15.2, C16.2, C17.2, C18.2, C19.2, C20.2, C21.2, C22.2, C23.2, C24.2, C25.2, C26.2, C27.2, C28.2, C29.2, C31.1, C31.2, C32.2, C33.2, C34.2, C35.2, C36.2, J1.2, R2.2, R10.2, R11.2, R12.2, R19.2, R20.2, R23.2, R26.2, R27.2, R29.2, R32.2, R34.2, U1.B1, U1.D8, U1.F1, U1.H9, U2.4, U3.3, U3.5, U3.17, U4.4, U4.PAD, U5.1, U5.25, U6.4, U6.5, U6.6, U7.1, U8.2, U11.2, U12.2, U13.2, U14.3, U14.PAD, U15.3, U15.4, U15.PAD, U16.1, U16.9, U16.17, U17.2, U19.C, U20.1, U20.3, U21.1, U21.3
NET_U1_A6: R7.1, U1.A6, U4.5
NET_U1_B5: R6.1, U1.B5, U4.6
NET_U1_B6: R10.1, U1.B6
NET_U1_C2: C11.1, U1.C2
NET_U1_C8: R12.1, U1.C8
NET_U1_D1: R9.1, U1.D1, U3.9
NET_U1_E2: R8.1, U1.E2, U3.10
NET_U1_E8: R4.1, U1.E8, U20.4
NET_U1_F7: C8.1, C9.1, F1.1, U1.F7
NET_U1_H7: R11.1, U1.H7
NET_U1_J3: C10.1, U1.J3
NET_U1_J9: U18.3, U18.4
NET_U2_3: R13.1, U2.3
NET_U2_7: R15.1, U2.7
NET_U3_4: R16.1, U3.4
NET_U3_11: R17.1, U3.11
NET_U4_3: R18.1, U4.3
NET_U5_4: C16.1, U5.4
NET_U5_22: R5.1, U5.22, U21.4
NET_U5_24: R20.1, U5.24
NET_U6_1: C19.1, U5.2, U6.1, U7.4, U8.1
NET_U6_2: U5.5, U6.2, U7.3
NET_U6_3: U5.6, U6.3, U7.2
NET_U8_3: R19.1, U8.3
NET_U8_4: U5.7, U8.4
NET_U14_1: C23.1, U14.1
NET_U14_6: R22.2, R23.1, U14.6
NET_U14_8: R21.1, U14.8
NET_U15_5: R24.1, U15.5
NET_U15_7: R25.2, R26.1, U15.7
NET_U16_3: C30.2, I1.1, U16.3, U16.4
NET_U16_6: C30.1, U16.6
NET_U16_7: C29.1, U16.7, U16.12
NET_U16_10: R29.1, U16.10
NET_U16_11: R27.1, R28.1, U16.11
NET_U16_ATNET_3: I1.2, R28.2
NET_U17_1: R31.1, R32.1, U17.1
NET_U17_3: R33.2, R34.1, U17.3
NET_U17_4: R30.1, U17.4, U20.2, U21.2
NET_U18_1: R2.1, U18.1, U18.2
PROC_SPI1_MISO: U1.B4, U2.2
PROC_SPI1_MOSI: U1.J7, U2.5
PROC_SPI1_NSS: R14.1, U1.A2, U2.1
PROC_SPI1_SCK: U1.A4, U2.6
PROC_USB_OTG_HS_ULPI_CK: U1.H6, U5.12
PROC_USB_OTG_HS_ULPI_D0: U1.G7, U5.16
PROC_USB_OTG_HS_ULPI_D1: U1.J6, U5.15
PROC_USB_OTG_HS_ULPI_D2: U1.J5, U5.14
PROC_USB_OTG_HS_ULPI_D3: U1.H3, U5.13
PROC_USB_OTG_HS_ULPI_D4: U1.J2, U5.11
PROC_USB_OTG_HS_ULPI_D5: U1.J1, U5.10
PROC_USB_OTG_HS_ULPI_D6: U1.H2, U5.9
PROC_USB_OTG_HS_ULPI_D7: U1.A5, U5.8
PROC_USB_OTG_HS_ULPI_DIR: U1.D7, U5.19
PROC_USB_OTG_HS_ULPI_NXT: U1.G8, U5.18
PROC_USB_OTG_HS_ULPI_STP: U1.G9, U5.20
VCC_S1_6V8: C24.1, C26.1, C28.1, C33.1, C34.1, J1.1, R21.2, U14.4, U15.8, U16.15, U16.16
VCC_TIER1_1V8: C1.1, C2.1, C3.1, C4.1, C5.1, C6.1, C7.1, C12.1, C13.1, C14.1, C17.1, C18.1, C25.1, C32.1, C35.1, C36.1, F1.2, R4.2, R5.2, R6.2, R7.2, R8.2, R9.2, R13.2, R14.2, R15.2, R16.2, R17.2, R18.2, R22.1, R30.2, R31.2, R33.1, U1.A8, U1.A9, U1.D9, U1.E1, U2.8, U3.14, U4.8, U5.17, U5.21, U14.5, U17.6, U20.5, U21.5
VCC_TIER1_3V3: C15.1, C20.1, C21.1, C22.1, C27.1, R24.2, R25.1, U5.3, U11.4, U12.4, U13.4, U15.1
VCC_TIER1_5V0: C31.2, I1.2, R28.2, U8.5, U16.8

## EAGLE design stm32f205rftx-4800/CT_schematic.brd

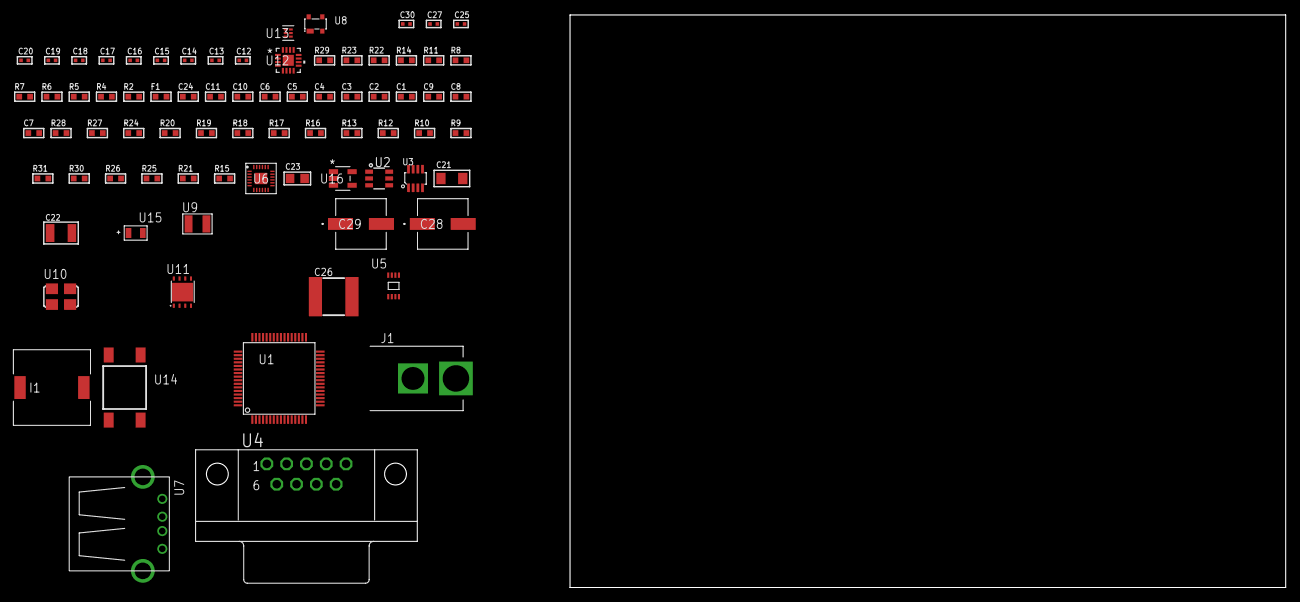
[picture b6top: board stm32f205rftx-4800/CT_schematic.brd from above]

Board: 2 copper layers, 100.0 x 80.0 mm, 78 parts (0 on the bottom side), 51 nets, no tracks yet.

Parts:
C1, C11, C24: 1e-06; C0603
C2, C3, C4, C5, C6: 1e-07; C0603
C7: 4.7e-06; C0603
C8, C9: 2.2e-06; C0603
C10: 1e-08; C0603
C12, C13: 1e-11; C0402
C14, C16, C17, C25, C27: 1e-07; C0402
C15, C18, C19, C20, C30: 1e-08; C0402
C21: 1e-05; C1206
C22: 1e-05; C1210
C23: 1e-05; C0805
C26: 6.8e-05; 2220
C28, C29: 0.0001; EXV-9H
F1: 240.0; L0603
I1: 5.2e-06; DR1040
J1: PJ-037B; PJ-037B_PACKAGE
R2, R23: 1000.0; R0603
R4: 4700.0; R0603
R5, R6, R7, R8: 2200.0; R0603
R9: 47000.0; R0603
R10, R12, R13, R16, R17, R18, R19, R20, R27, R28: 10000.0; R0603
R11: 1270.0; R0603
R14: 120.0; R0603
R15, R21: 100000.0; R0603
R22: 2231.0; R0603
R24: 20000.0; R0603
R25: 150000.0; R0603
R26: 300000.0; R0603
R29: 9100.0; R0603
R30: 680000.0; R0603
R31: 120000.0; R0603
U1: STM32F205RFT6; LQFP64
U2: MAX4995AAUT+T; SOT-23-6
U3: MAX3051EKA+T; SOT-23-8
U4: 182-009-113R531; 182-009-MALE
U5: 24AA32AT-I/MNY; TDFN-8/6MM
U6: MPU-9250; QFN24_2
U7: 61400416021; USB-A-H
U8: prtr5v0u2ax; SOT143B
U9: ABS07-32.768KHZ-7-T
U10: ASFL1-25MHZ-NCS; ASFL1
U11: LP3878SDX-ADJ/NOPB; WSON-8
U12: LTC3601EUD#PBF; QFN-16_EP
U13: TPS3895ADRYR; SON-6
U14: 4-1437565-2; SW_4-1437565-2
U15: Q65110A2395; LGM67K-G1J2-24-Z
U16: nc7sz125m5x; NC7SZ125M5X

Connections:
CLK_CRYSTAL_U1_3: C12.1, U1.3, U9.1
CLK_CRYSTAL_U1_4: C13.1, U1.4, U9.2
CLK_U1_5: U1.5, U10.3
GND: C1.2, C2.2, C3.2, C4.2, C5.2, C6.2, C7.2, C8.2, C9.2, C10.2, C11.2, C12.2, C13.2, C14.2, C15.2, C16.2, C17.2, C18.2, C19.2, C20.2, C21.2, C22.2, C23.2, C24.2, C26.1, C26.2, C27.2, C28.2, C29.2, C30.2, J1.2, R2.2, R9.2, R10.2, R11.2, R13.2, R15.2, R16.2, R18.2, R23.2, R24.2, R26.2, R29.2, R31.2, U1.12, U1.18, U1.63, U2.2, U3.2, U4.5, U5.4, U5.7, U6.18, U6.20, U6.25, U7.4, U7.5, U7.6, U8.1, U10.2, U11.3, U11.PAD, U12.1, U12.9, U12.17, U13.2, U15.C, U16.1, U16.3
NET_U1_7: R4.1, U1.7, U16.4
NET_U1_13: C10.1, C11.1, F1.1, U1.13
NET_U1_29: R7.1, U1.29, U5.6
NET_U1_30: R8.1, U1.30, U5.5
NET_U1_31: C8.1, U1.31
NET_U1_43: R11.1, U1.43
NET_U1_47: C9.1, U1.47
NET_U1_57: U14.3, U14.4
NET_U1_58: R5.1, U1.58, U6.23
NET_U1_59: R6.1, U1.59, U6.24
NET_U1_60: R10.1, U1.60
NET_U2_3: R9.1, U2.3
NET_U3_6: R14.2, U3.6
NET_U3_8: R15.1, U3.8
NET_U4_2: R14.2, U3.6, U4.2
NET_U4_3: R14.1, U3.7, U4.3
NET_U5_1: R16.1, U5.1
NET_U5_2: R17.1, U5.2
NET_U5_3: R18.1, U5.3
NET_U6_9: R20.1, U6.9
NET_U6_10: C16.1, U6.10
NET_U6_22: R19.1, U6.22
NET_U11_1: C20.1, U11.1
NET_U11_6: R22.2, R23.1, U11.6
NET_U11_8: R21.1, U11.8
NET_U12_3: C25.2, I1.1, U12.3, U12.4
NET_U12_6: C25.1, U12.6
NET_U12_7: C24.1, U12.7, U12.12
NET_U12_10: R26.1, U12.10
NET_U12_11: R24.1, R25.1, U12.11
NET_U12_ATNET_3: I1.2, R25.2
NET_U13_1: R28.1, R29.1, U13.1
NET_U13_3: R30.2, R31.1, U13.3
NET_U13_4: R27.1, U13.4, U16.2
NET_U14_1: R2.1, U14.1, U14.2
PROC_CAN1_RX: U1.61, U3.4
PROC_CAN1_TX: U1.62, U3.1
PROC_GPIO_TO_U1_USB_FAULT: R12.1, U1.6, U2.6
PROC_GPIO_TO_U1_VBUS_EN: R13.1, U1.2, U2.4
PROC_GPIO_TO_U6_FSYNC: U1.9, U6.11
PROC_GPIO_TO_U6_INT_B: U1.8, U6.12
PROC_USB_OTG_FS_DM: U1.44, U7.2, U8.3
PROC_USB_OTG_FS_DP: U1.45, U7.3, U8.2
PROC_USB_OTG_FS_VBUS: U1.42, U2.1, U7.1, U8.4
VCC_S1_6V4: C21.1, C23.1, C28.1, C29.1, J1.1, R21.2, U11.4, U12.15, U12.16
VCC_TIER1_3V3: C1.1, C2.1, C3.1, C4.1, C5.1, C6.1, C7.1, C14.1, C15.1, C17.1, C18.1, C19.1, C22.1, C27.1, C30.1, F1.2, R4.2, R5.2, R6.2, R7.2, R8.2, R12.2, R17.2, R19.2, R20.2, R22.1, R27.2, R28.2, R30.1, U1.1, U1.19, U1.32, U1.48, U1.64, U3.3, U5.8, U6.1, U6.8, U6.13, U10.4, U11.5, U13.6, U16.5
VCC_TIER1_5V0: C26.2, I1.2, R25.2, U2.5, U12.8
